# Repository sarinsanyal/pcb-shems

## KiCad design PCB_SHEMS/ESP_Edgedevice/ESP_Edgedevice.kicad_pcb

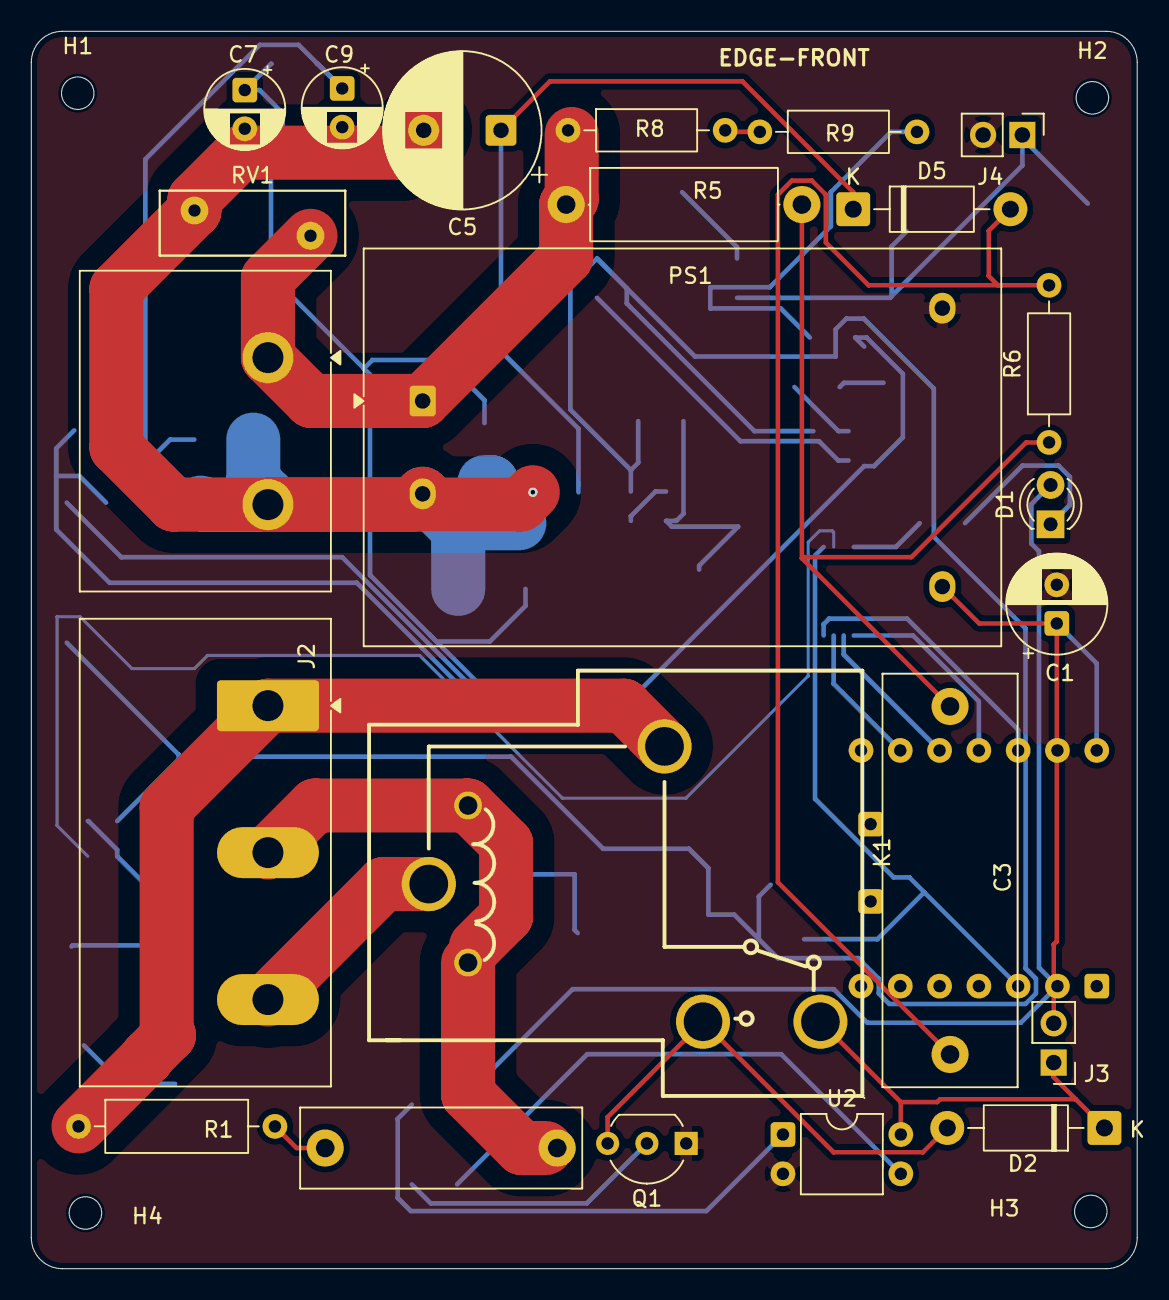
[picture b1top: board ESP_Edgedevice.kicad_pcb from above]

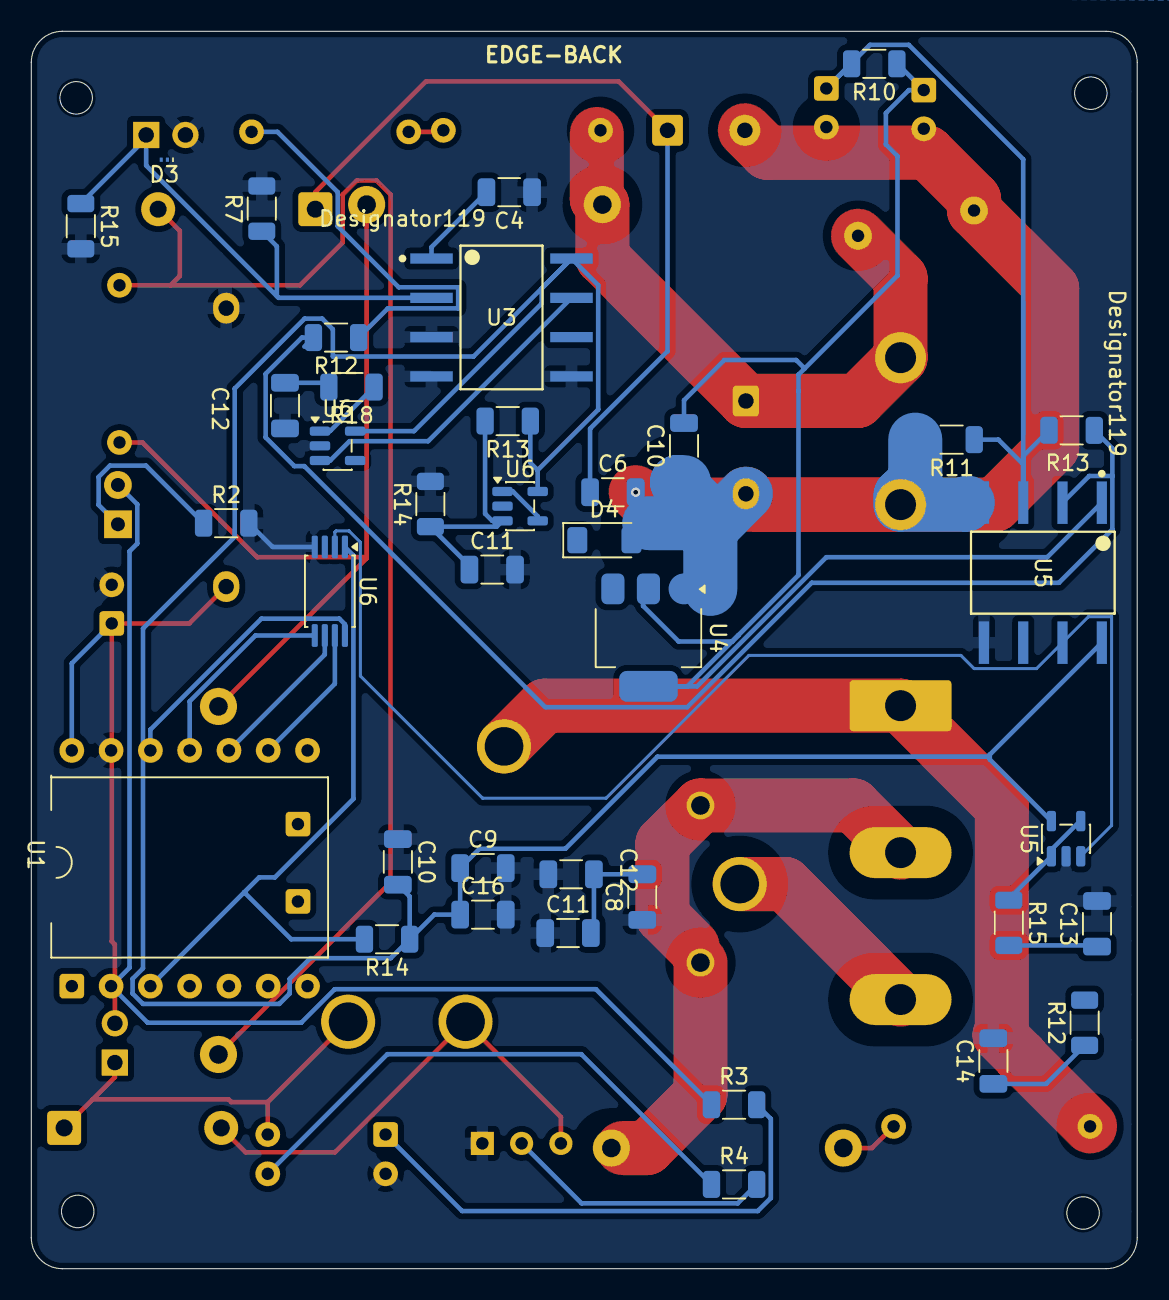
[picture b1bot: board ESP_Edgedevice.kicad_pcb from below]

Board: 2 copper layers, 71.5 x 80.0 mm, 65 parts (38 on the bottom side), 39 nets.

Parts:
C1: 470uF; CP_Radial_D6.3mm_P2.50mm
C2: 100nF X2, 275 V AC; C_Rect_L18.0mm_W5.0mm_P15.00mm_FKS3_FKP3
C3: 470nF X2; C_Rect_L26.5mm_W8.5mm_P22.50mm_MKS4
C4, C8, C9#2, C10, C11, C11#2, C12, C12#2, C13, C14, C16: 100nF; C_1206_3216Metric
C5: 470uF; CP_Radial_D10.0mm_P5.00mm
C6: 10uF; C_1206_3216Metric
C7, C9: 10uF; CP_Radial_D5.0mm_P2.50mm
C10#2: 0.1uF; C_1206_3216Metric
D1: LED; LED_D3.0mm
D2, D5: 1N4007; D_DO-41_SOD81_P10.16mm_Horizontal
D3: D_TVS; Nexperia_DSN0603-2_0.6x0.3mm_P0.4mm
D4: 7.5; D_MiniMELF
H1, H2, H3, H4: MountingHole; MountingHole_2.1mm
J1: Barrier Terminal; TerminalBlock_Ningbo-Kagnex_HB9500M_1x02_P9.5mm
J2: HB9500-9.5-3P; TerminalBlock_Ningbo-Kagnex_HB9500M_1x03_P9.5mm
J3: Conn_01x02_Pin; PinHeader_1x02_P2.54mm_Vertical
J4: Conn_01x02; PinHeader_1x02_P2.54mm_Vertical
K1: SLA-05VDC-SL-C; RELAY-TH_SLA-XXVDC-XX-C
PS1: HLK-5M05; Converter_ACDC_Hi-Link_HLK-5Mxx
Q1: S8050; TO-92_Inline_Wide
R1: 100R; R_Axial_DIN0309_L9.0mm_D3.2mm_P12.70mm_Horizontal
R2, R4, R13#2: 1K; R_1206_3216Metric
R3, R12, R15#2, R18: 1k; R_1206_3216Metric
R5: 220R 1W; R_Axial_DIN0414_L11.9mm_D4.5mm_P15.24mm_Horizontal
R6: 470k; R_Axial_DIN0207_L6.3mm_D2.5mm_P10.16mm_Horizontal
R7: 2.7 Ω, 1206; R_1206_3216Metric
R8, R9: 1M; R_Axial_DIN0207_L6.3mm_D2.5mm_P10.16mm_Horizontal
R10, R11: 100K; R_1206_3216Metric
R12#2: 220K; R_1206_3216Metric
R13, R14, R14#2: 10k; R_1206_3216Metric
R15: 1.2 Ω, (Not 15A); R_1206_3216Metric
RV1: Varistor; RV_Disc_D12mm_W4.2mm_P7.5mm
U1: XIAO ESP32C3; XIAO_Socket_W15.24
U2: PC817X3NSZ1B; DIP-4_W7.62mm
U3, U5: AMC1200SDUBR; DUB0008A-IPC_A
U4: AMS1117-5.0; SOT-223-3_TabPin2
U5#2, U6, U6#2: OPA333xxDBV; SOT-23-5
U6#3: MCP3202; TSSOP-8_4.4x3mm_P0.65mm

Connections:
/+3.3V: C8.2, C9#2.1, C10.2, C11#2.2, C12#2.2, C16.1, R13.1, R14#2.1, U1.12 (VCC_3V3), U3.8 (VDD2), U5.8 (VDD2), U5#2.5 (V+), U6.5 (V+), U6#2.5 (V+), U6#3.8 (VDD/VREF)
/Relay/Jd_VCC: D2.1 (K), J3.1, K1.1, U2.4
/Relay/Relay: D2.2 (A), K1.2, Q1.3 (C)
/voltagesensing.kicad_sch/I_ADC: C12.2, R18.2
/voltagesensing.kicad_sch/I_OUT_P: U3.7 (VOUTP), U6#2.3 (+), U6#3.3 (CH1)
/voltagesensing.kicad_sch/VBIAS: C11.1, R13.2, R14.1, U6.3 (+)
/voltagesensing.kicad_sch/VBIAS_BUF: U6.1, U6.4 (-)
/voltagesensing.kicad_sch/VCC: C4.2, U3.1 (VDD1)
/voltagesensing.kicad_sch/VDD1: C7.1, C10#2.2, R10.1, U4.2 (VO), U5.1 (VDD1)
/voltagesensing.kicad_sch/V_ADC: C13.1, R15#2.2
/voltagesensing.kicad_sch/V_OUT_P: U5.7 (VOUTP), U5#2.3 (+), U6#3.2 (CH0)
COM: C2.2, J2.2, K1.3, K1.4
D2: R14#2.2, U1.3 (D2), U6#3.1 (~CS/SHDN)
D8: U1.9 (D8), U6#3.7 (CLK)
D9: U1.10 (D9), U6#3.6 (DOUT)
D10: U1.11 (D10), U6#3.5 (DIN)
GND: C1.2, C4.1, C8.1, C9#2.2, C10.1, C11.2, C11#2.1, C12.1, C12#2.1, C13.2, C14.2, C16.2, D3.2 (A2), J4.2, PS1.3 (-Vout), Q1.1 (E), R2.2, R7.2, R14.2, R15.2, U1.13 (GND), U2.2, U3.3 (VINN), U3.4 (GND1), U3.5 (GND2), U5.5 (GND2), U5#2.2 (V-), U6.2 (V-), U6#2.2 (V-), U6#3.4 (VSS)
LIVE: J1.1, PS1.1 (AC/L), R5.1, R8.1, RV1.1
NC: J2.3, K1.6
NEUTRAL: C5.2, C6.2, C7.2, C9.2, C10#2.1, D4.2 (A), J1.2, PS1.2 (AC/N), R11.2, RV1.2, U4.1 (GND), U5.4 (GND1)
NO: J2.1, K1.5, R1.1
unnamed: C2.1, R1.2
unnamed: C3.1, R5.2, R6.1
unnamed: D1.1 (K), R2.1
unnamed: D3.1 (A1), J4.1, R7.1, R15.1, U3.2 (VINP)
unnamed: C3.2, D4.1 (K), D5.2 (A), R6.2
unnamed: C5.1, C6.1, D5.1 (K), U4.3 (VI)
unnamed: Q1.2 (B), R4.2
unnamed: R3.2, U2.1
unnamed: R4.1, U2.3
unnamed: R8.2, R9.1
unnamed: R9.2, R12#2.1
unnamed: R15#2.1, U5#2.1, U5#2.4 (-)
unnamed: C9.1, R10.2, R11.1, R13#2.2, U5.3 (VINN)
unnamed: R12#2.2, R13#2.1, U5.2 (VINP)
unnamed: R18.1, U6#2.1, U6#2.4 (-)
unnamed: C14.1, R12.1
RELAY_IN: D1.2 (A), R3.1, U1.2 (D1)
VCC: C1.1, J3.2, PS1.4 (+Vout), U1.14 (VUSB)
